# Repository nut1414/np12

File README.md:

# np12
 yet another 12 keys macro pad using [QMK Firmware](https://github.com/qmk/qmk_firmware)

## Parts
 - a generic Arduino Pro Micro (or other pin compatible)
 - 12x MX Switches
 - an EC11 encoder
 - *(Optional)* a 6mm button for entering the bootloader
 - *(Optional)* 12x Kailh hot-swap sockets
 - *(Optional)* PJ320a TRRS Jack if you want to do a split-board

## Pin Configuration
 |Row|Pin|Arduino Wire Pin|
 |:--:|:--:|:--:|
 |0|D7|6|
 |1|E6|7|
 |2|B4|8|
 |3*|F6|A1|

 |Col|Pin|Arduino Wire Pin|
 |:--:|:--:|:--:|
 |0|D1|2|
 |1|D0|3|
 |2|D4|4|
 |3|C6|5|
 |4*|F7|A0|
 
 *Used only for rotary encoder switch.
 
 |Pin|Arduino Wire Pin||
 |:--:|:--:|:--:|
 |PF5,PF4|A2,A3|Used for encoder|
 |PD2|RX1|Used for handling serial on TRRS audio jack|

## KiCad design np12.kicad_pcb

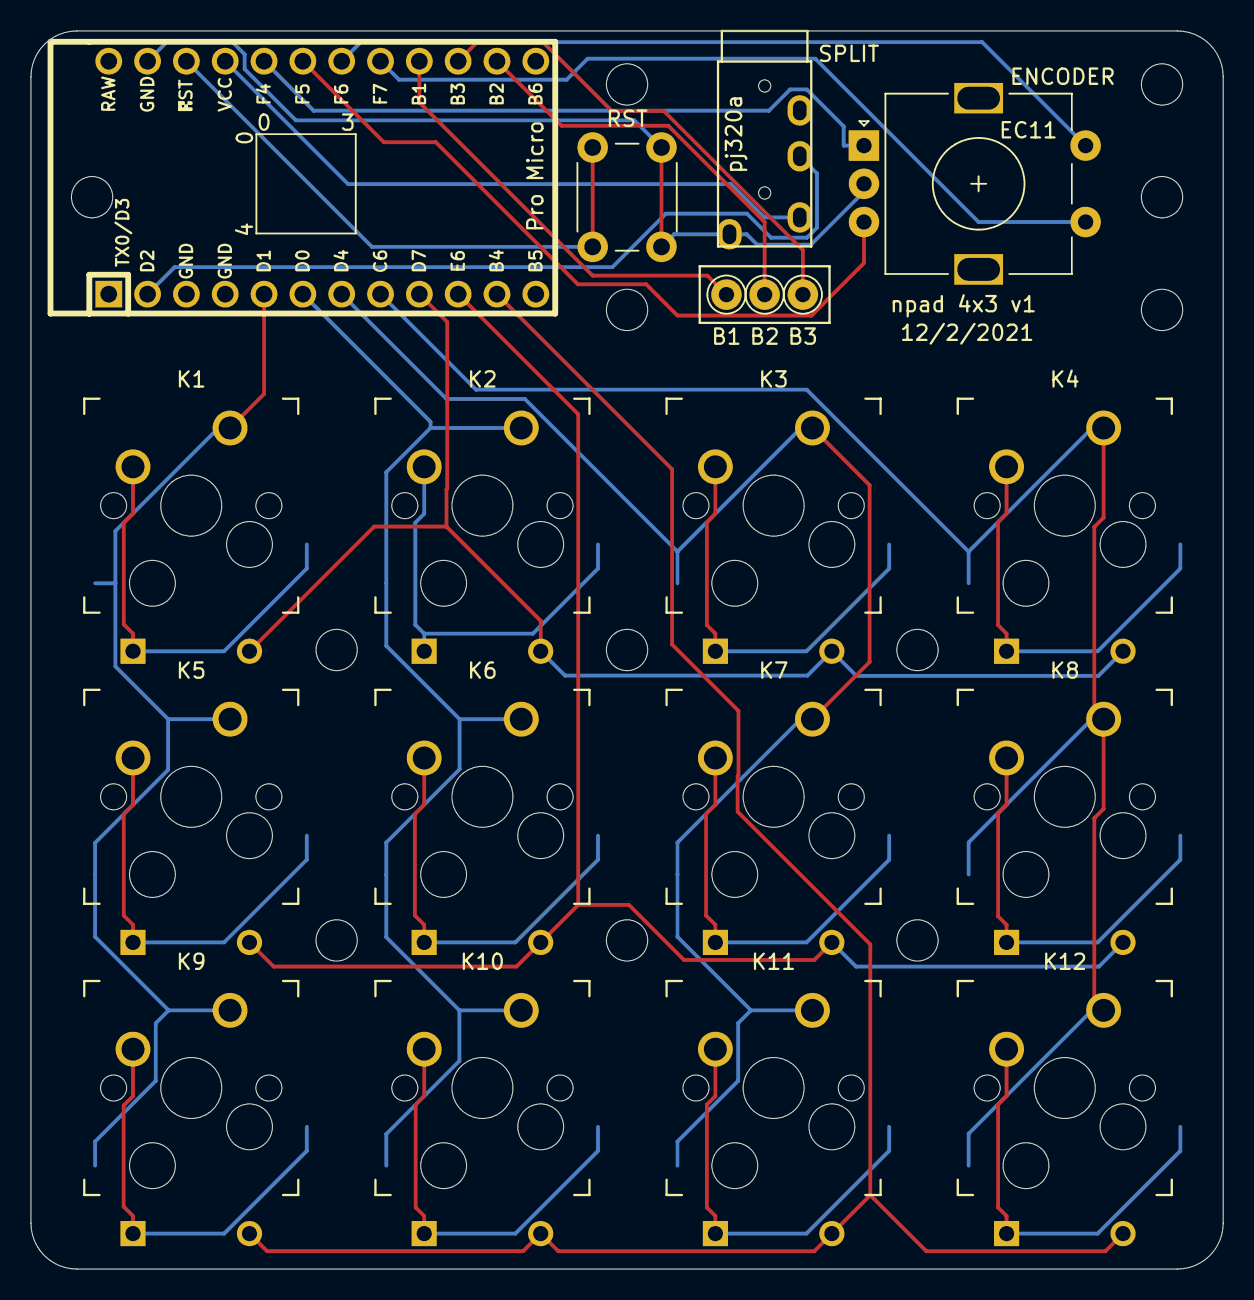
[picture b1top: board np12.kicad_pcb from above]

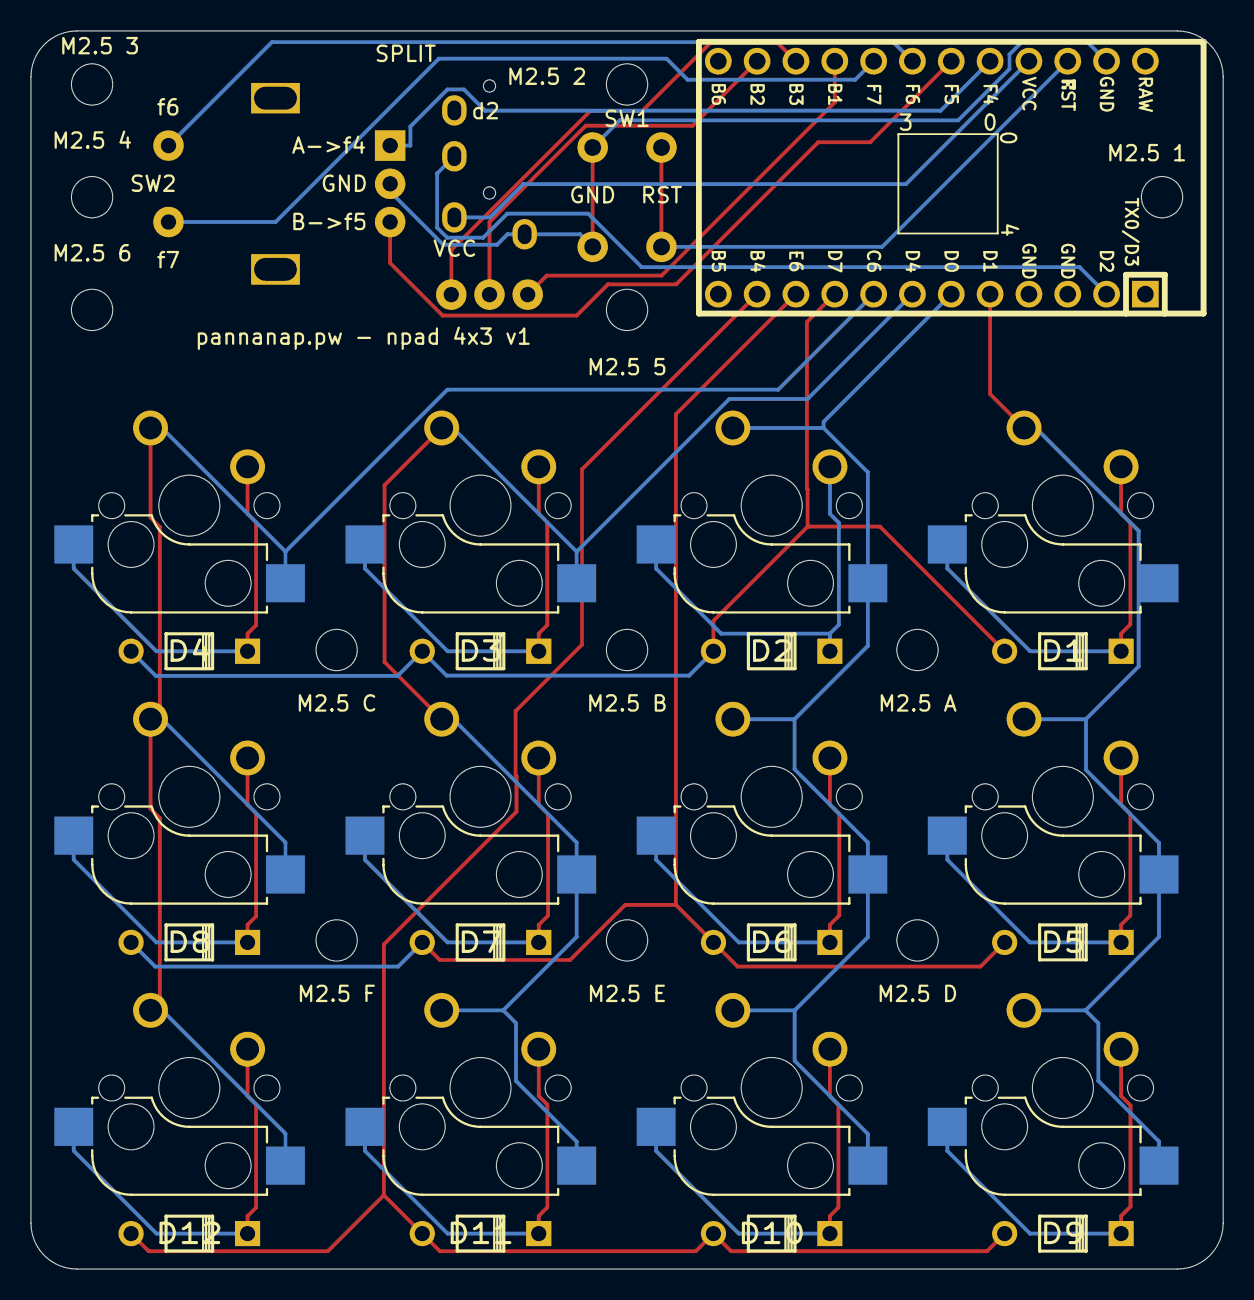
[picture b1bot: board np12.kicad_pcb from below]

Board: 2 copper layers, 78.0 x 81.0 mm, 43 parts (12 on the bottom side), 30 nets.

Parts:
B1, B2, B3: Pin_D1.0mm_L10.0mm
D1, D2, D3, D4, D5, D6, D7, D8, D9, D10, D11, D12: D; Diode
K1, K2, K3, K4, K5, K6, K7, K8, K9, K10, K11, K12: KEYSW; Kailh_socket_MX_optional
M2.5 1, M2.5 2, M2.5 3, M2.5 4, M2.5 5, M2.5 6, M2.5 A, M2.5 B, M2.5 C, M2.5 D, M2.5 E, M2.5 F: MountingHole_2.7mm_M2.5
SW1: SW_Push; SW_PUSH_6mm
SW2: Rotary_Encoder_Switch; RotaryEncoder_Alps_EC11E-Switch_Vertical_H20mm
U1: ProMicro; ArduinoProMicro
U2: TRRS; TRRS-PJ-320A

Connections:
/b1: B1.1, U1.16
/b2: B2.1, U1.14
/b3: B3.1, U1.15
/col0: K1.1, K5.1, K9.1, U1.5
/col1: K2.1, K6.1, K10.1, U1.6
/col2: K3.1, K7.1, K11.1, U1.7
/col3: K4.1, K8.1, K12.1, U1.8
/data: U1.2, U2.3
/row0: D1.1, D2.1, D3.1, D4.1, U1.9
/row1: D5.1, D6.1, D7.1, D8.1, U1.10
/row2: D9.1, D10.1, D11.1, D12.1, U1.11
unnamed: D1.2, K1.2
unnamed: D2.2, K2.2
unnamed: D3.2, K3.2
unnamed: D4.2, K4.2
unnamed: D5.2, K5.2
unnamed: D6.2, K6.2
unnamed: D7.2, K7.2
unnamed: D8.2, K8.2
unnamed: D9.2, K9.2
unnamed: D10.2, K10.2
unnamed: D11.2, K11.2
unnamed: D12.2, K12.2
unnamed: SW1.1, SW2.C, U1.23, U2.1
unnamed: SW1.2, U1.22
unnamed: SW2.A, U1.20
unnamed: SW2.B, U1.19
unnamed: SW2.S1, U1.17
unnamed: SW2.S2, U1.18
VCC: U1.21, U2.2

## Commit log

2021-03-16 Update Schematic
2021-04-08 change split data trrs ring to ring 1
